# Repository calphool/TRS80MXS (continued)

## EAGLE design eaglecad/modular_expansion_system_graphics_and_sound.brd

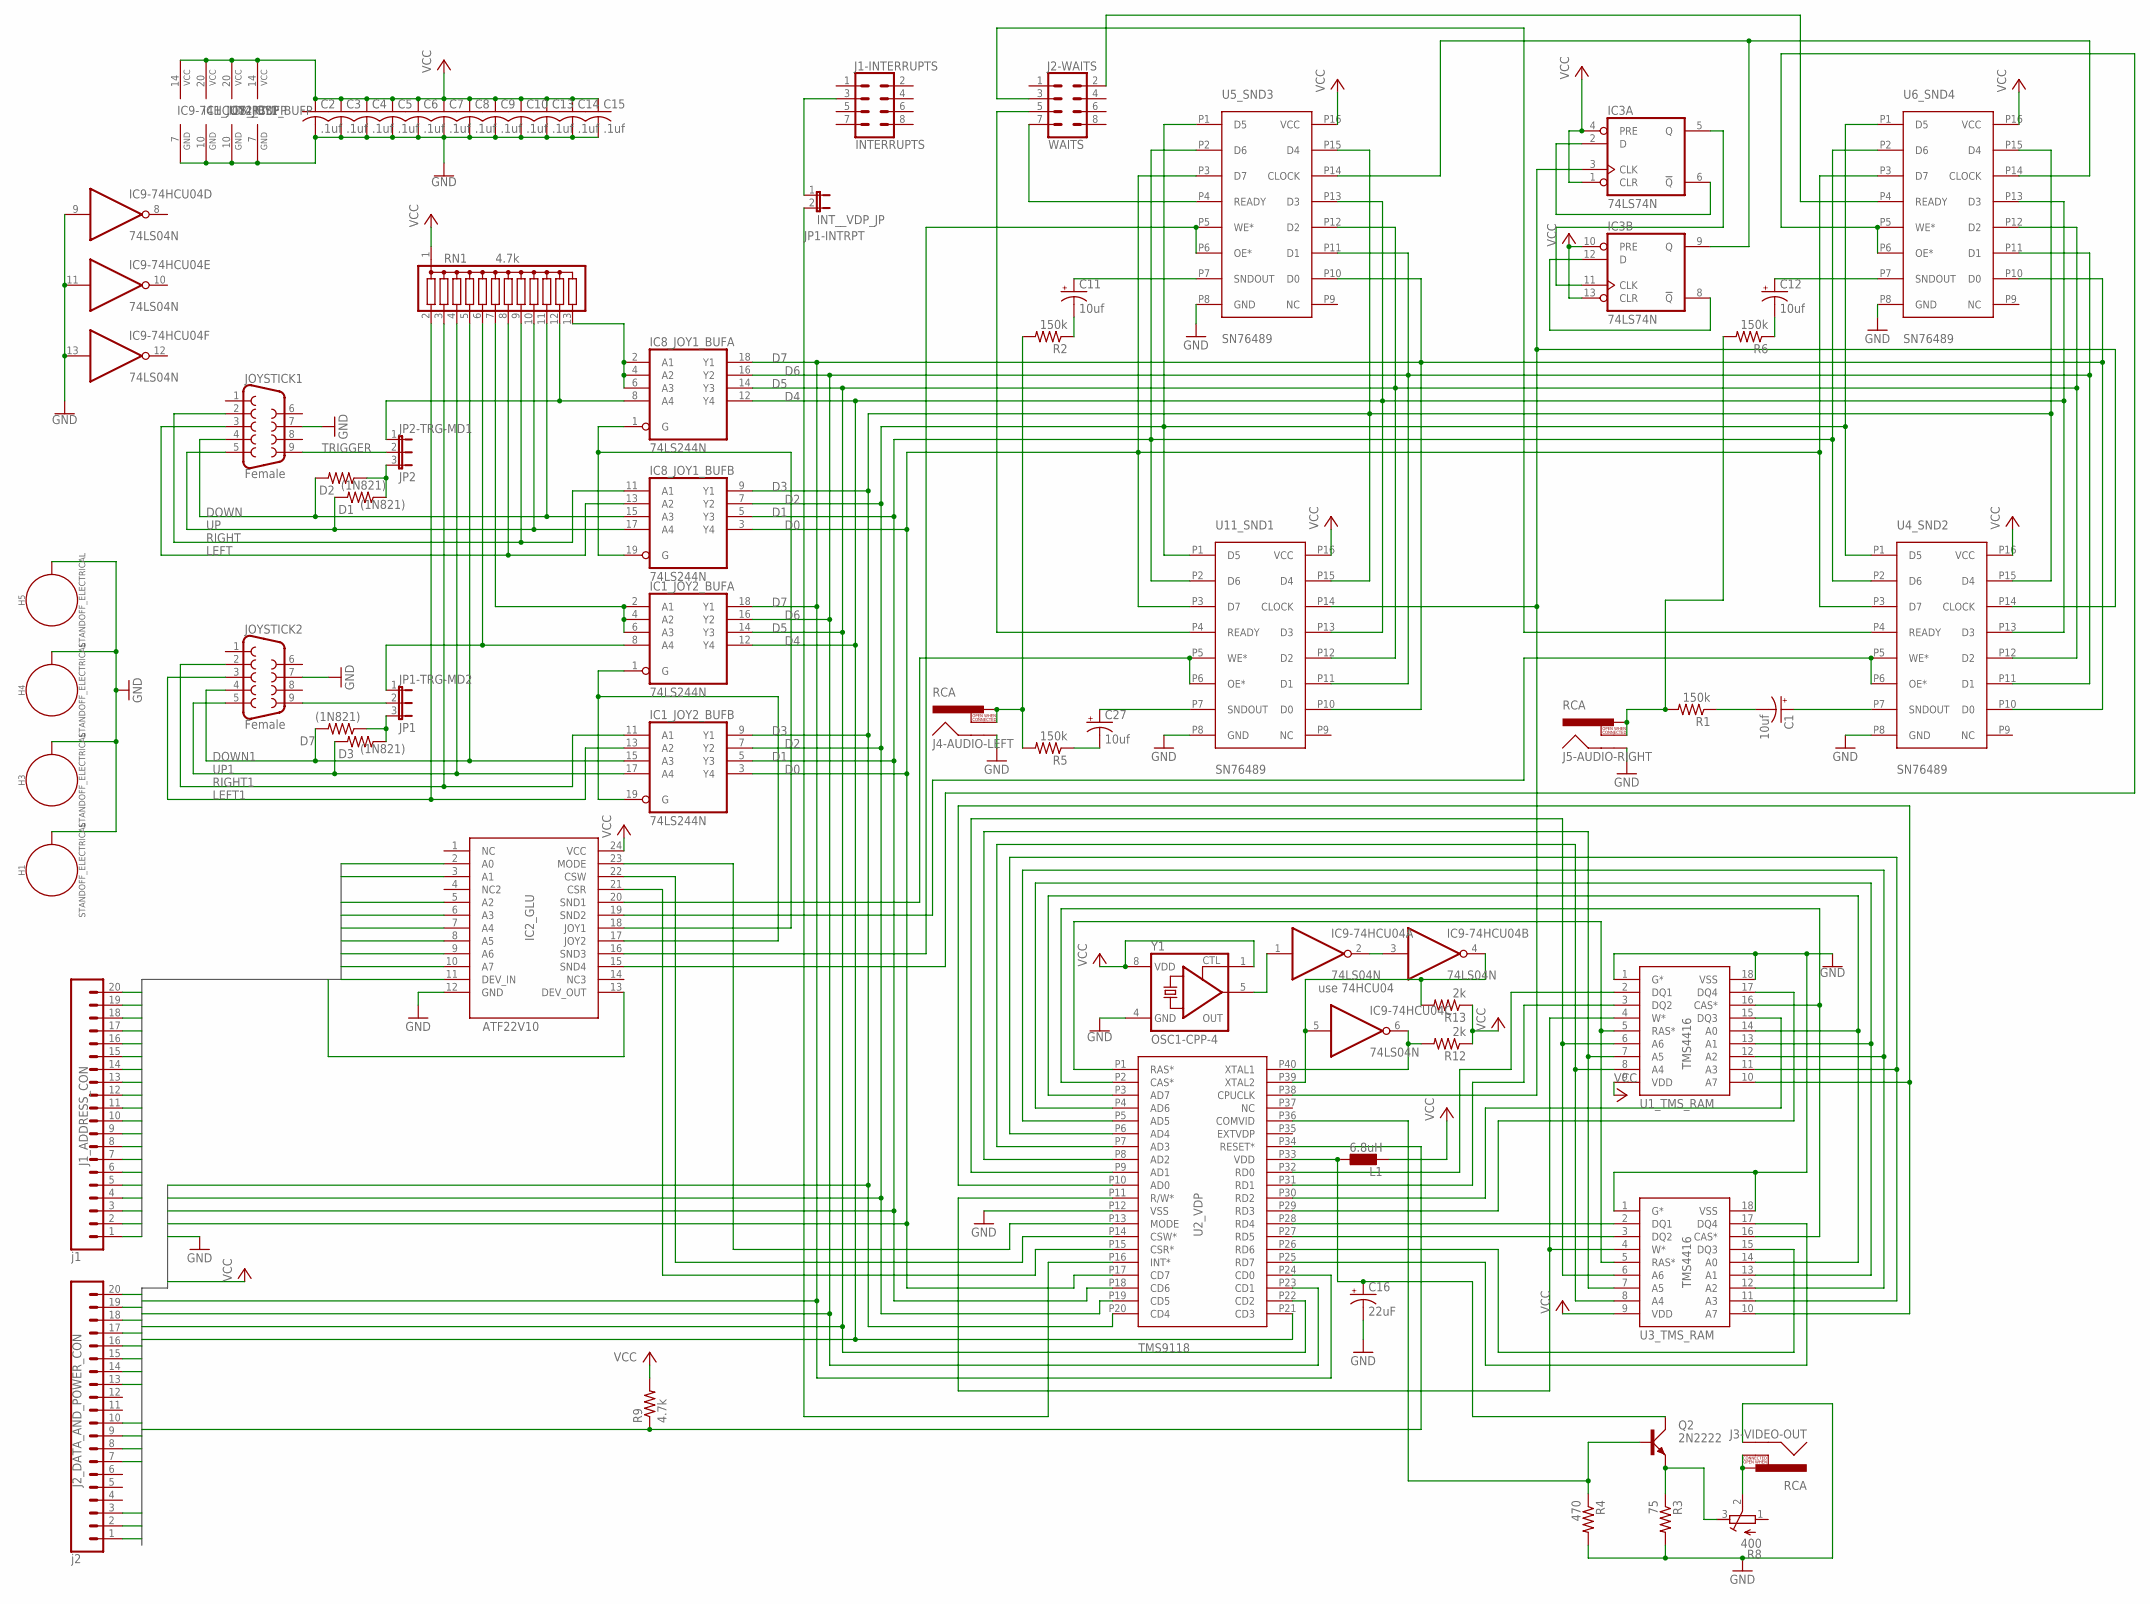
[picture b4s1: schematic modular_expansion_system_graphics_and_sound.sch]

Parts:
C1, C11, C12, C27: 10uf; E2,5-6
C2, C3, C4, C5, C6, C7, C8, C9, C10, C13, C14, C15: .1uf; C025-024X044
C16: 22uF; E2,5-5
D1, D2, D3, D7: (1N821); 0204V
H1, H3, H4, H5: STANDOFF_ELECTRICAL; STANDOFF-ELECTRICAL
IC1_JOY2_BUF, IC8_JOY1_BUF: 74LS244N; DIL20
IC2_GLU: ATF22V10; DIP24SKI
IC3: 74LS74N; DIL14
IC9-74HCU04: 74LS04N; DIL14
J1-INTERRUPTS: INTERRUPTS; 2X4
J1_ADDRESS_CON: j1; 1X20
J2-WAITS: WAITS; 2X4
J2_DATA_AND_POWER_CON: j2; 1X20
J3-VIDEO-OUT, J4-AUDIO-LEFT, J5-AUDIO-RIGHT: RCA
JOYSTICK1, JOYSTICK2: Female; DB9
JP1-INTRPT: INT__VDP_JP; JP1
JP1-TRG-MD2: JP1; JP2
JP2-TRG-MD1: JP2
L1: 6.8uH; 0207/10
Q2: 2N2222; TO18A
R1, R2, R5, R6: 150k; 0207/2V
R3: 75; 0207/2V
R4: 470; 0207/2V
R8: 400; RTRIM64W
R9: 4.7k; 0207/2V
R12, R13: 2k; 0207/2V
RN1: 4.7k; SIL13
U1_TMS_RAM, U3_TMS_RAM: TMS4416; DIP18
U2_VDP: TMS9118; DIP40_MCU
U4_SND2, U5_SND3, U6_SND4, U11_SND1: SN76489; DIP16
Y1: OSC1-CPP-4; CPP-4

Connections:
5_BIT_TRIGGER_LINE: IC8_JOY1_BUF.8 (A4), JP2-TRG-MD1.1, RN1.12
5_BIT_TRIGGER_LINE_2: IC1_JOY2_BUF.8 (A4), JP1-TRG-MD2.1, RN1.6
A0: IC2_GLU.2 (A0), J1_ADDRESS_CON.1
A1: IC2_GLU.3 (A1), J1_ADDRESS_CON.2
A2: IC2_GLU.5 (A2), J1_ADDRESS_CON.3
A3: IC2_GLU.6 (A3), J1_ADDRESS_CON.4
A4: IC2_GLU.7 (A4), J1_ADDRESS_CON.5
A5: IC2_GLU.8 (A5), J1_ADDRESS_CON.6
A6: IC2_GLU.9 (A6), J1_ADDRESS_CON.7
A7: IC2_GLU.10 (A7), J1_ADDRESS_CON.8
A8: J1_ADDRESS_CON.9
A9: J1_ADDRESS_CON.10
A10: J1_ADDRESS_CON.11
A11: J1_ADDRESS_CON.12
A12: J1_ADDRESS_CON.13
A13: J1_ADDRESS_CON.14
A14: J1_ADDRESS_CON.15
A15: J1_ADDRESS_CON.16
CAS*: J2_DATA_AND_POWER_CON.9
CLK-IN-1: IC9-74HCU04.6 (O), R12.2, U2_VDP.P40 (XTAL1)
CLK-IN-2: IC9-74HCU04.4 (O), IC9-74HCU04.5 (I), R13.2, U2_VDP.P39 (XTAL2)
CLK-OUT: IC9-74HCU04.1 (I), Y1.5 (OUT)
CLOCK_DIV_4: IC3.9 (Q), U5_SND3.P14 (CLOCK), U6_SND4.P14 (CLOCK)
COMVID: Q2.B, R4.1, U2_VDP.P36 (COMVID)
COMVID-OUT: Q2.E, R3.1, R8.3 (E)
CSR: IC2_GLU.21 (CSR), U2_VDP.P15 (CSR*)
CSW: IC2_GLU.22 (CSW), U2_VDP.P14 (CSW*)
D0: IC1_JOY2_BUF.3 (Y4), IC8_JOY1_BUF.3 (Y4), J2_DATA_AND_POWER_CON.20, U2_VDP.P17 (CD7), U4_SND2.P3 (D7), U5_SND3.P3 (D7), U6_SND4.P3 (D7), U11_SND1.P3 (D7)
D1: IC1_JOY2_BUF.5 (Y3), IC8_JOY1_BUF.5 (Y3), J2_DATA_AND_POWER_CON.19, U2_VDP.P18 (CD6), U4_SND2.P2 (D6), U5_SND3.P2 (D6), U6_SND4.P2 (D6), U11_SND1.P2 (D6)
D2: IC1_JOY2_BUF.7 (Y2), IC8_JOY1_BUF.7 (Y2), J2_DATA_AND_POWER_CON.18, U2_VDP.P19 (CD5), U4_SND2.P1 (D5), U5_SND3.P1 (D5), U6_SND4.P1 (D5), U11_SND1.P1 (D5)
D3: IC1_JOY2_BUF.9 (Y1), IC8_JOY1_BUF.9 (Y1), J2_DATA_AND_POWER_CON.17, U2_VDP.P20 (CD4), U4_SND2.P15 (D4), U5_SND3.P15 (D4), U6_SND4.P15 (D4), U11_SND1.P15 (D4)
D4: IC1_JOY2_BUF.12 (Y4), IC8_JOY1_BUF.12 (Y4), J2_DATA_AND_POWER_CON.16, U2_VDP.P21 (CD3), U4_SND2.P13 (D3), U5_SND3.P13 (D3), U6_SND4.P13 (D3), U11_SND1.P13 (D3)
D5: IC1_JOY2_BUF.14 (Y3), IC8_JOY1_BUF.14 (Y3), J2_DATA_AND_POWER_CON.15, U2_VDP.P22 (CD2), U4_SND2.P12 (D2), U5_SND3.P12 (D2), U6_SND4.P12 (D2), U11_SND1.P12 (D2)
D6: IC1_JOY2_BUF.16 (Y2), IC8_JOY1_BUF.16 (Y2), J2_DATA_AND_POWER_CON.14, U2_VDP.P23 (CD1), U4_SND2.P11 (D1), U5_SND3.P11 (D1), U6_SND4.P11 (D1), U11_SND1.P11 (D1)
D7: IC1_JOY2_BUF.18 (Y1), IC8_JOY1_BUF.18 (Y1), J2_DATA_AND_POWER_CON.13, U2_VDP.P24 (CD0), U4_SND2.P10 (D0), U5_SND3.P10 (D0), U6_SND4.P10 (D0), U11_SND1.P10 (D0)
DOWN: D2.2, IC8_JOY1_BUF.15 (A3), JOYSTICK1.4, RN1.11
DOWN1: D7.2, IC1_JOY2_BUF.15 (A3), JOYSTICK2.4, RN1.5
GND: C2.2, C3.2, C4.2, C5.2, C6.2, C7.2, C8.2, C9.2, C10.2, C13.2, C14.2, C15.2, C16.-, H1.P1, H3.P1, H4.P1, H5.P1, IC1_JOY2_BUF.10 (GND), IC2_GLU.12 (GND), IC3.7 (GND), IC8_JOY1_BUF.10 (GND), IC9-74HCU04.7 (GND), IC9-74HCU04.9 (I), IC9-74HCU04.11 (I), IC9-74HCU04.13 (I), J2_DATA_AND_POWER_CON.2, J3-VIDEO-OUT.SHELL, J4-AUDIO-LEFT.SHELL, J5-AUDIO-RIGHT.SHELL, JOYSTICK1.7, JOYSTICK2.7, R3.2, R4.2, U1_TMS_RAM.1 (G*), U1_TMS_RAM.18 (VSS), U2_VDP.P12 (VSS), U3_TMS_RAM.1 (G*), U3_TMS_RAM.18 (VSS), U4_SND2.P8 (GND), U5_SND3.P8 (GND), U6_SND4.P8 (GND), U11_SND1.P8 (GND), Y1.4 (GND)
IN*: IC2_GLU.11 (DEV_IN), J1_ADDRESS_CON.17
INTAK*: J2_DATA_AND_POWER_CON.7
JOY1_IN_ENABLE_N: IC2_GLU.18 (JOY1), IC8_JOY1_BUF.1 (G), IC8_JOY1_BUF.19 (G)
JOY2_IN_ENABLE_N: IC1_JOY2_BUF.1 (G), IC1_JOY2_BUF.19 (G), IC2_GLU.17 (JOY2)
LEFT: IC8_JOY1_BUF.13 (A2), JOYSTICK1.3, RN1.8
LEFT1: IC1_JOY2_BUF.13 (A2), JOYSTICK2.3, RN1.2
unnamed: J4-AUDIO-LEFT.PIN, J4-AUDIO-LEFT.SWITCH, R2.2, R5.2
unnamed: J1-INTERRUPTS.3, JP1-INTRPT.1
unnamed: JP1-INTRPT.2, U2_VDP.P16 (INT*)
unnamed: J3-VIDEO-OUT.PIN, J3-VIDEO-OUT.SWITCH, R8.2 (S)
unnamed: C12.-, R6.1
unnamed: IC3.5 (Q), IC3.11 (CLK)
unnamed: IC3.8 (!Q), IC3.12 (D)
unnamed: C11.+, U5_SND3.P7 (SNDOUT)
unnamed: IC9-74HCU04.2 (O), IC9-74HCU04.3 (I)
unnamed: C12.+, U6_SND4.P7 (SNDOUT)
unnamed: IC3.2 (D), IC3.6 (!Q)
unnamed: C1.-, R1.1
unnamed: C11.-, R2.1
unnamed: U1_TMS_RAM.5 (RAS*), U2_VDP.P1 (RAS*), U3_TMS_RAM.5 (RAS*)
unnamed: U1_TMS_RAM.16 (CAS*), U2_VDP.P2 (CAS*), U3_TMS_RAM.16 (CAS*)
unnamed: J5-AUDIO-RIGHT.PIN, J5-AUDIO-RIGHT.SWITCH, R1.2, R6.2
unnamed: C27.-, R5.1
OUT*: IC2_GLU.13 (DEV_OUT), J1_ADDRESS_CON.18
RAS*: J2_DATA_AND_POWER_CON.10
RD*: J1_ADDRESS_CON.19
RIGHT: IC8_JOY1_BUF.11 (A1), JOYSTICK1.2, RN1.9
RIGHT1: IC1_JOY2_BUF.11 (A1), JOYSTICK2.2, RN1.3
SN76489-CLOCK: IC3.3 (CLK), U2_VDP.P38 (CPUCLK), U4_SND2.P14 (CLOCK), U11_SND1.P14 (CLOCK)
SND1_ENABLE_N: IC2_GLU.20 (SND1), U11_SND1.P5 (WE*), U11_SND1.P6 (OE*)
SND1_READY: J2-WAITS.5, U11_SND1.P4 (READY)
SND2_ENABLE_N: IC2_GLU.19 (SND2), U4_SND2.P5 (WE*), U4_SND2.P6 (OE*)
SND2_READY: J2-WAITS.3, U4_SND2.P4 (READY)
SND3_ENABLE_N: IC2_GLU.16 (SND3), U5_SND3.P5 (WE*), U5_SND3.P6 (OE*)
SND3_READY: J2-WAITS.7, U5_SND3.P4 (READY)
SND4_ENABLE_N: IC2_GLU.15 (SND4), U6_SND4.P5 (WE*), U6_SND4.P6 (OE*)
SND4_READY: J2-WAITS.2, U6_SND4.P4 (READY)
SNDOUT1: C27.+, U11_SND1.P7 (SNDOUT)
SNDOUT2: C1.+, U4_SND2.P7 (SNDOUT)
SYSRES*: J2_DATA_AND_POWER_CON.8, R9.1, U2_VDP.P34 (RESET*)
TIED-HIGH-1: IC8_JOY1_BUF.2 (A1), IC8_JOY1_BUF.4 (A2), IC8_JOY1_BUF.6 (A3), RN1.13
TIED-HIGH-2: IC1_JOY2_BUF.2 (A1), IC1_JOY2_BUF.4 (A2), IC1_JOY2_BUF.6 (A3), RN1.7
TMS9118_RW(*)_TMS4416_W(*): U1_TMS_RAM.4 (W*), U2_VDP.P11 (R/W*), U3_TMS_RAM.4 (W*)
TMS9918_AD0-TMS4416_A7: U1_TMS_RAM.10 (A7), U2_VDP.P10 (AD0), U3_TMS_RAM.10 (A7)
TMS9918_AD1-TMS4416_A6: U1_TMS_RAM.6 (A6), U2_VDP.P9 (AD1), U3_TMS_RAM.6 (A6)
TMS9918_AD2-TMS4416_A5: U1_TMS_RAM.7 (A5), U2_VDP.P8 (AD2), U3_TMS_RAM.7 (A5)
TMS9918_AD3-TMS4416_A4: U1_TMS_RAM.8 (A4), U2_VDP.P7 (AD3), U3_TMS_RAM.8 (A4)
TMS9918_AD4-TMS4416_A3: U1_TMS_RAM.11 (A3), U2_VDP.P6 (AD4), U3_TMS_RAM.11 (A3)
TMS9918_AD5-TMS4416_A2: U1_TMS_RAM.12 (A2), U2_VDP.P5 (AD5), U3_TMS_RAM.12 (A2)
TMS9918_AD6-TMS4416_A1: U1_TMS_RAM.13 (A1), U2_VDP.P4 (AD6), U3_TMS_RAM.13 (A1)
TMS9918_AD7-TMS4416_A0: U1_TMS_RAM.14 (A0), U2_VDP.P3 (AD7), U3_TMS_RAM.14 (A0)
TOPOFDIODES: D1.1, D2.1, JP2-TRG-MD1.3
TOPOFDIODES1: D3.1, D7.1, JP1-TRG-MD2.3
TRIGGER: JOYSTICK1.9, JP2-TRG-MD1.2
TRIGGER1: JOYSTICK2.9, JP1-TRG-MD2.2
UP: D1.2, IC8_JOY1_BUF.17 (A4), JOYSTICK1.5, RN1.10
UP1: D3.2, IC1_JOY2_BUF.17 (A4), JOYSTICK2.5, RN1.4
VCC: C2.1, C3.1, C4.1, C5.1, C6.1, C7.1, C8.1, C9.1, C10.1, C13.1, C14.1, C15.1, IC1_JOY2_BUF.20 (VCC), IC2_GLU.24 (VCC), IC3.1 (CLR), IC3.4 (PRE), IC3.10 (PRE), IC3.13 (CLR), IC3.14 (VCC), IC8_JOY1_BUF.20 (VCC), IC9-74HCU04.14 (VCC), J2_DATA_AND_POWER_CON.1, L1.2, R9.2, R12.1, R13.1, RN1.1, U1_TMS_RAM.9 (VDD), U3_TMS_RAM.9 (VDD), U4_SND2.P16 (VCC), U5_SND3.P16 (VCC), U6_SND4.P16 (VCC), U11_SND1.P16 (VCC), Y1.1 (CTL), Y1.8 (VDD)
VCC/2: J2_DATA_AND_POWER_CON.3
VDP-RD0: U1_TMS_RAM.2 (DQ1), U2_VDP.P32 (RD0)
VDP-RD1: U1_TMS_RAM.3 (DQ2), U2_VDP.P31 (RD1)
VDP-RD2: U1_TMS_RAM.15 (DQ3), U2_VDP.P30 (RD2)
VDP-RD3: U1_TMS_RAM.17 (DQ4), U2_VDP.P29 (RD3)
VDP-RD4: U2_VDP.P28 (RD4), U3_TMS_RAM.2 (DQ1)
VDP-RD5: U2_VDP.P27 (RD5), U3_TMS_RAM.3 (DQ2)
VDP-RD6: U2_VDP.P26 (RD6), U3_TMS_RAM.15 (DQ3)
VDP-RD7: U2_VDP.P25 (RD7), U3_TMS_RAM.17 (DQ4)
VDP_MODE: IC2_GLU.23 (MODE), U2_VDP.P13 (MODE)
VID-VCC: C16.+, L1.1, Q2.C, U2_VDP.P33 (VDD)
WR*: J1_ADDRESS_CON.20

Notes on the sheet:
use 74HCU04

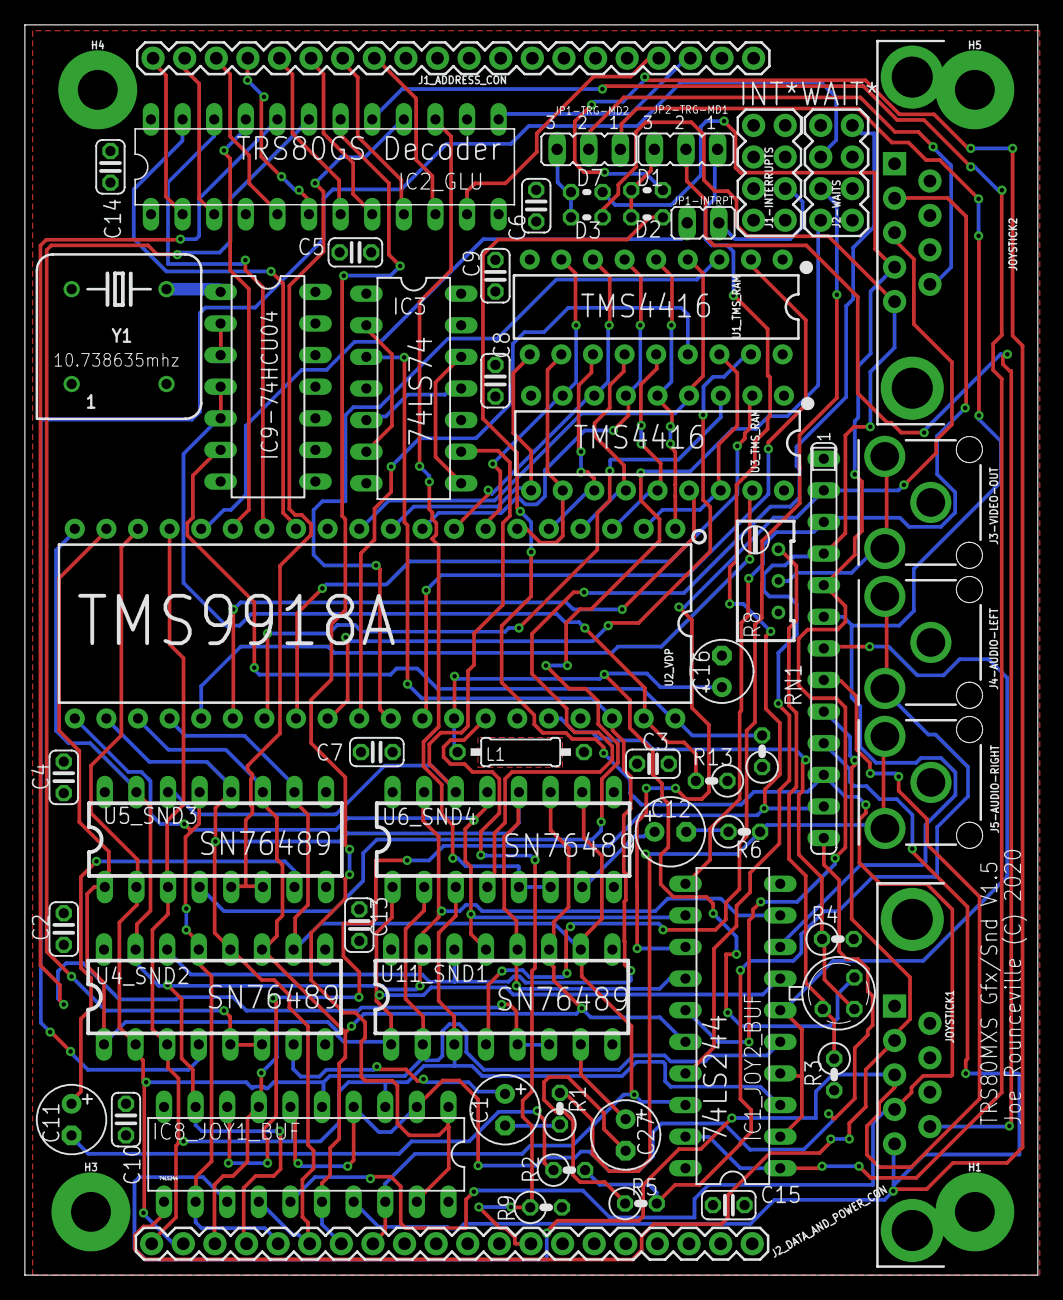
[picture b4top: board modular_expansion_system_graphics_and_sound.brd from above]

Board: 2 copper layers, 81.4 x 100.5 mm, 63 parts (0 on the bottom side), 94 nets.

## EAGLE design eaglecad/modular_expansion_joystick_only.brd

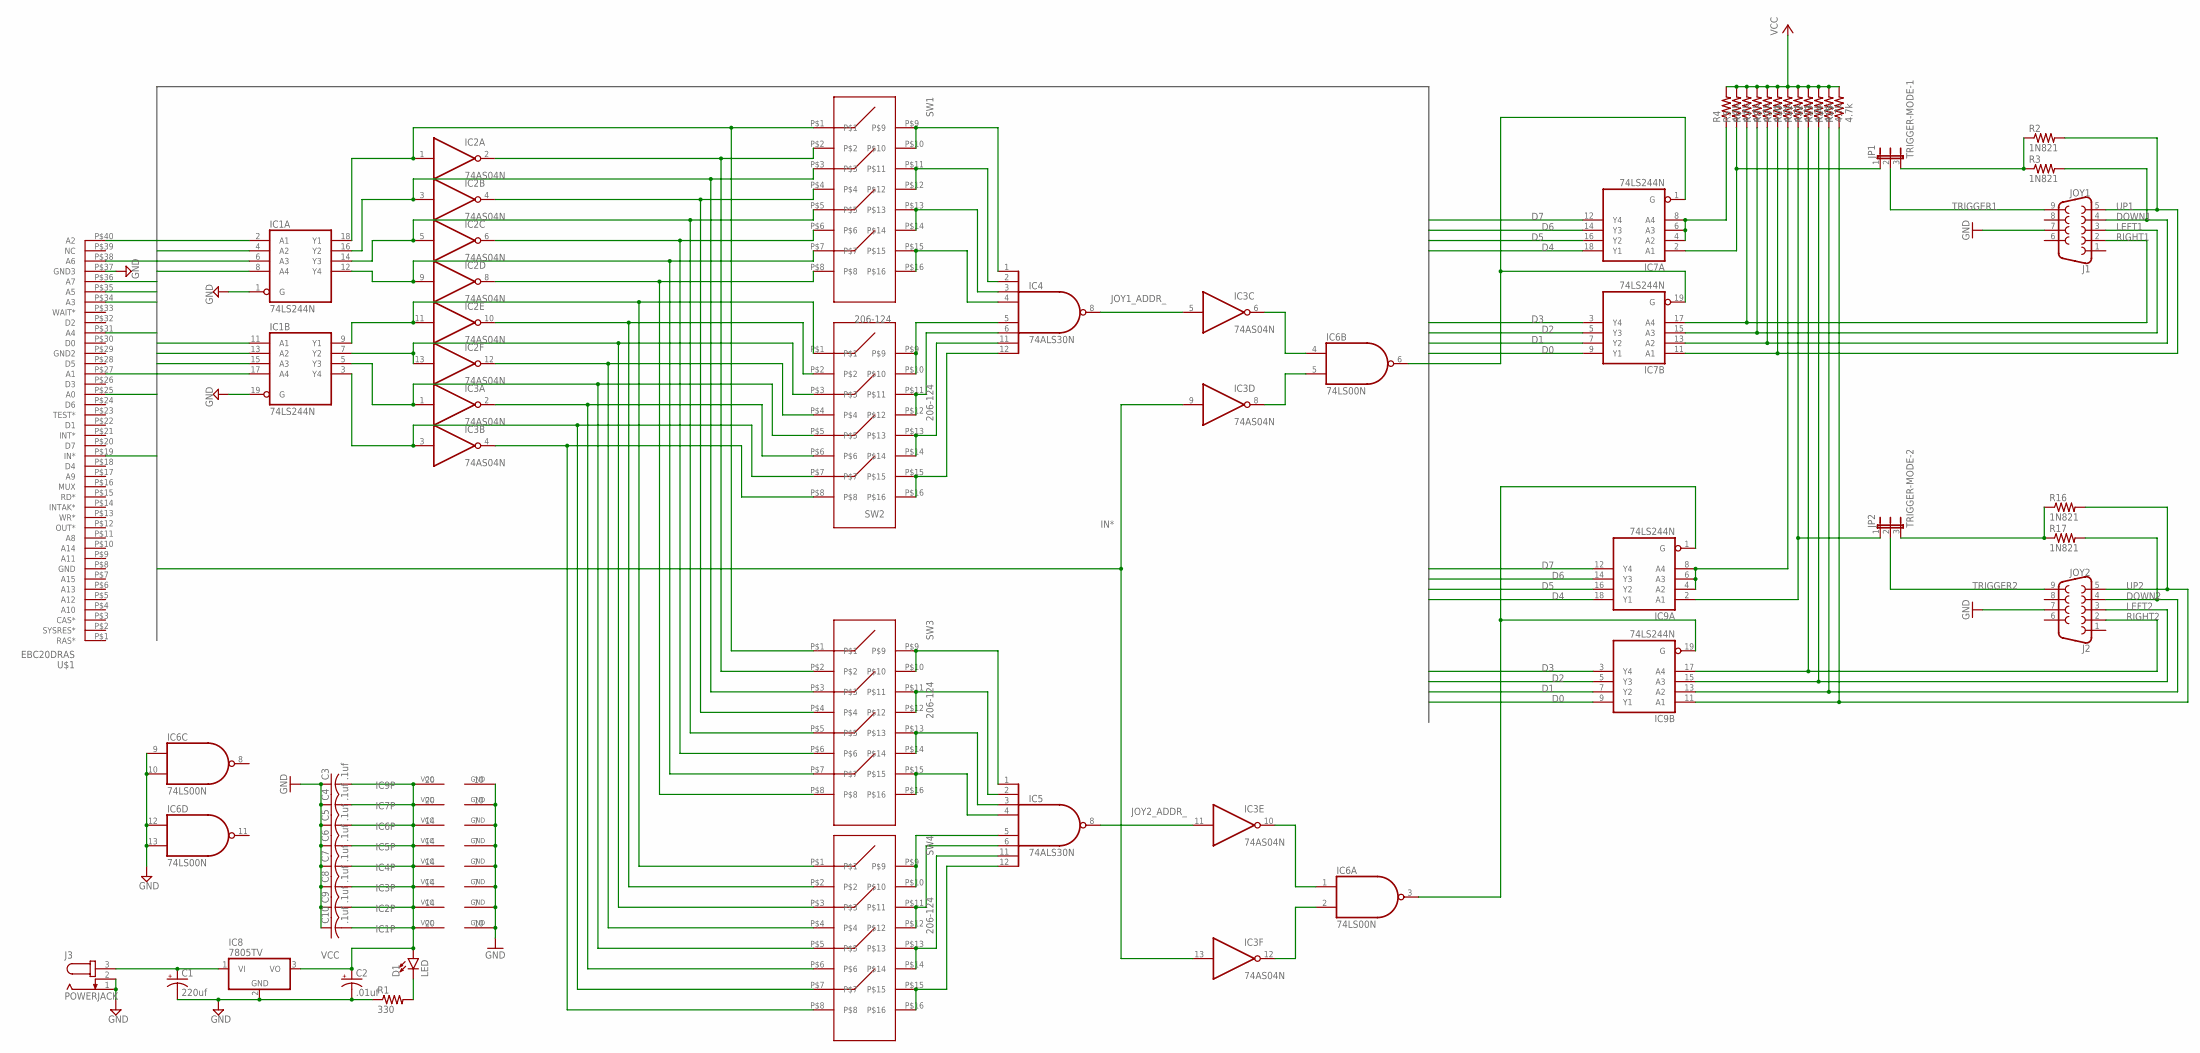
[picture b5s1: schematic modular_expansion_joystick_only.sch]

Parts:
C1: 220uf; E3,5-10
C2: .01uf; E2,5-6E
C3, C4, C5, C6, C7, C8, C9, C10: .1uf; C025-025X050
D1: LED; LED_3MM
IC1, IC7, IC9: 74LS244N; DIL20
IC2, IC3: 74AS04N; DIL14
IC4, IC5: 74ALS30N; DIL14
IC6: 74LS00N; DIL14
IC8: 7805TV; TO220V
J1: JOY1; DB9
J2: JOY2; DB9
J3: POWERJACK; SPC4077
JP1: TRIGGER-MODE-1; JP2
JP2: TRIGGER-MODE-2; JP2
R1: 330; 0204V
R2, R3, R16, R17: 1N821; 0204V
R4, R5, R6, R7, R8, R9, R10, R11, R12, R13, R14, R15: 4.7k; 0204/5
SW1, SW2, SW3, SW4: 206-124
U$1: EBC20DRAS

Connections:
A0: IC1.2 (A1), U$1.P$25 (A0)
A1: IC1.4 (A2), U$1.P$27 (A1)
A2: IC1.6 (A3), U$1.P$40 (A2)
A3: IC1.8 (A4), U$1.P$34 (A3)
A4: IC1.11 (A1), U$1.P$31 (A4)
A5: IC1.13 (A2), U$1.P$35 (A5)
A6: IC1.15 (A3), U$1.P$38 (A6)
A7: IC1.17 (A4), U$1.P$36 (A7)
D0: IC7.9 (Y1), IC9.9 (Y1)
D1: IC7.7 (Y2), IC9.7 (Y2)
D2: IC7.5 (Y3), IC9.5 (Y3)
D3: IC7.3 (Y4), IC9.3 (Y4)
D4: IC7.18 (Y1), IC9.18 (Y1)
D5: IC7.16 (Y2), IC9.16 (Y2)
D6: IC7.14 (Y3), IC9.14 (Y3)
D7: IC7.12 (Y4), IC9.12 (Y4)
DOWN1: IC7.13 (A2), J1.4, R3.2, R8.1
DOWN2: IC9.13 (A2), J2.4, R14.1, R17.2
GND: C1.-, C2.-, C3.1, C4.1, C5.1, C6.1, C7.1, C8.1, C9.1, C10.1, IC1.1 (G), IC1.10 (GND), IC1.19 (G), IC2.7 (GND), IC3.7 (GND), IC4.7 (GND), IC5.7 (GND), IC6.7 (GND), IC6.9 (I0), IC6.10 (I1), IC6.12 (I0), IC6.13 (I1), IC7.10 (GND), IC8.2 (GND), IC9.10 (GND), J1.7, J2.7, J3.1, J3.2, R1.1, U$1.P$37 (GND3)
IN*: IC3.9 (I), IC3.13 (I), U$1.P$19 (IN*)
JOY1_ADDR_: IC3.5 (I), IC4.8 (O)
JOY1_SELECTED_: IC6.6 (O), IC7.1 (G), IC7.19 (G)
JOY2_ADDR_: IC3.11 (I), IC5.8 (O)
JOY2_SELECTED_: IC6.3 (O), IC9.1 (G), IC9.19 (G)
LEFT1: IC7.15 (A3), J1.3, R7.1
LEFT2: IC9.15 (A3), J2.3, R13.1
unnamed: IC1.18 (Y1), IC2.1 (I), SW1.P$1, SW3.P$1
unnamed: IC1.16 (Y2), IC2.3 (I), SW1.P$3, SW3.P$3
unnamed: IC1.14 (Y3), IC2.5 (I), SW1.P$5, SW3.P$5
unnamed: IC1.12 (Y4), IC2.9 (I), SW1.P$7, SW3.P$7
unnamed: IC1.9 (Y1), IC2.11 (I), SW2.P$1, SW4.P$1
unnamed: IC1.7 (Y2), IC2.13 (I), SW2.P$3, SW4.P$3
unnamed: IC1.5 (Y3), IC3.1 (I), SW2.P$5, SW4.P$5
unnamed: IC1.3 (Y4), IC3.3 (I), SW2.P$7, SW4.P$7
unnamed: IC2.2 (O), SW1.P$2, SW3.P$2
unnamed: IC2.4 (O), SW1.P$4, SW3.P$4
unnamed: IC2.6 (O), SW1.P$6, SW3.P$6
unnamed: IC2.8 (O), SW1.P$8, SW3.P$8
unnamed: IC2.10 (O), SW2.P$2, SW4.P$2
unnamed: IC2.12 (O), SW2.P$4, SW4.P$4
unnamed: IC3.2 (O), SW2.P$6, SW4.P$6
unnamed: IC4.1 (I0), SW1.P$9, SW1.P$10
unnamed: IC4.2 (I1), SW1.P$11, SW1.P$12
unnamed: IC4.3 (I2), SW1.P$13, SW1.P$14
unnamed: IC3.4 (O), SW2.P$8, SW4.P$8
unnamed: IC4.4 (I3), SW1.P$15, SW1.P$16
unnamed: IC4.5 (I4), SW2.P$9, SW2.P$10
unnamed: IC4.6 (I5), SW2.P$11, SW2.P$12
unnamed: IC4.11 (I6), SW2.P$13, SW2.P$14
unnamed: IC4.12 (I7), SW2.P$15, SW2.P$16
unnamed: IC3.6 (O), IC6.4 (I0)
unnamed: IC3.8 (O), IC6.5 (I1)
unnamed: IC3.12 (O), IC6.2 (I1)
unnamed: IC3.10 (O), IC6.1 (I0)
unnamed: IC5.1 (I0), SW3.P$9, SW3.P$10
unnamed: IC5.2 (I1), SW3.P$11, SW3.P$12
unnamed: IC5.3 (I2), SW3.P$13, SW3.P$14
unnamed: IC5.4 (I3), SW3.P$15, SW3.P$16
unnamed: IC5.5 (I4), SW4.P$9, SW4.P$10
unnamed: IC5.6 (I5), SW4.P$11, SW4.P$12
unnamed: IC5.11 (I6), SW4.P$13, SW4.P$14
unnamed: IC5.12 (I7), SW4.P$15, SW4.P$16
unnamed: JP2.3, R16.1, R17.1
unnamed: C1.+, IC8.1 (VI), J3.3
unnamed: JP1.3, R2.1, R3.1
unnamed: IC9.4 (A2), IC9.6 (A3), IC9.8 (A4), R10.1
unnamed: D1.K (C), R1.2
unnamed: IC9.2 (A1), JP2.1, R11.1
unnamed: IC7.4 (A2), IC7.6 (A3), IC7.8 (A4), R4.1
unnamed: IC7.2 (A1), JP1.1, R5.1
RIGHT1: IC7.17 (A4), J1.2, R6.1
RIGHT2: IC9.17 (A4), J2.2, R12.1
TRIGGER1: J1.9, JP1.2
TRIGGER2: J2.9, JP2.2
UP1: IC7.11 (A1), J1.5, R2.2, R9.1
UP2: IC9.11 (A1), J2.5, R15.1, R16.2
VCC: C2.+, C3.2, C4.2, C5.2, C6.2, C7.2, C8.2, C9.2, C10.2, D1.A, IC1.20 (VCC), IC2.14 (VCC), IC3.14 (VCC), IC4.14 (VCC), IC5.14 (VCC), IC6.14 (VCC), IC7.20 (VCC), IC8.3 (VO), IC9.20 (VCC), R4.2, R5.2, R6.2, R7.2, R8.2, R9.2, R10.2, R11.2, R12.2, R13.2, R14.2, R15.2

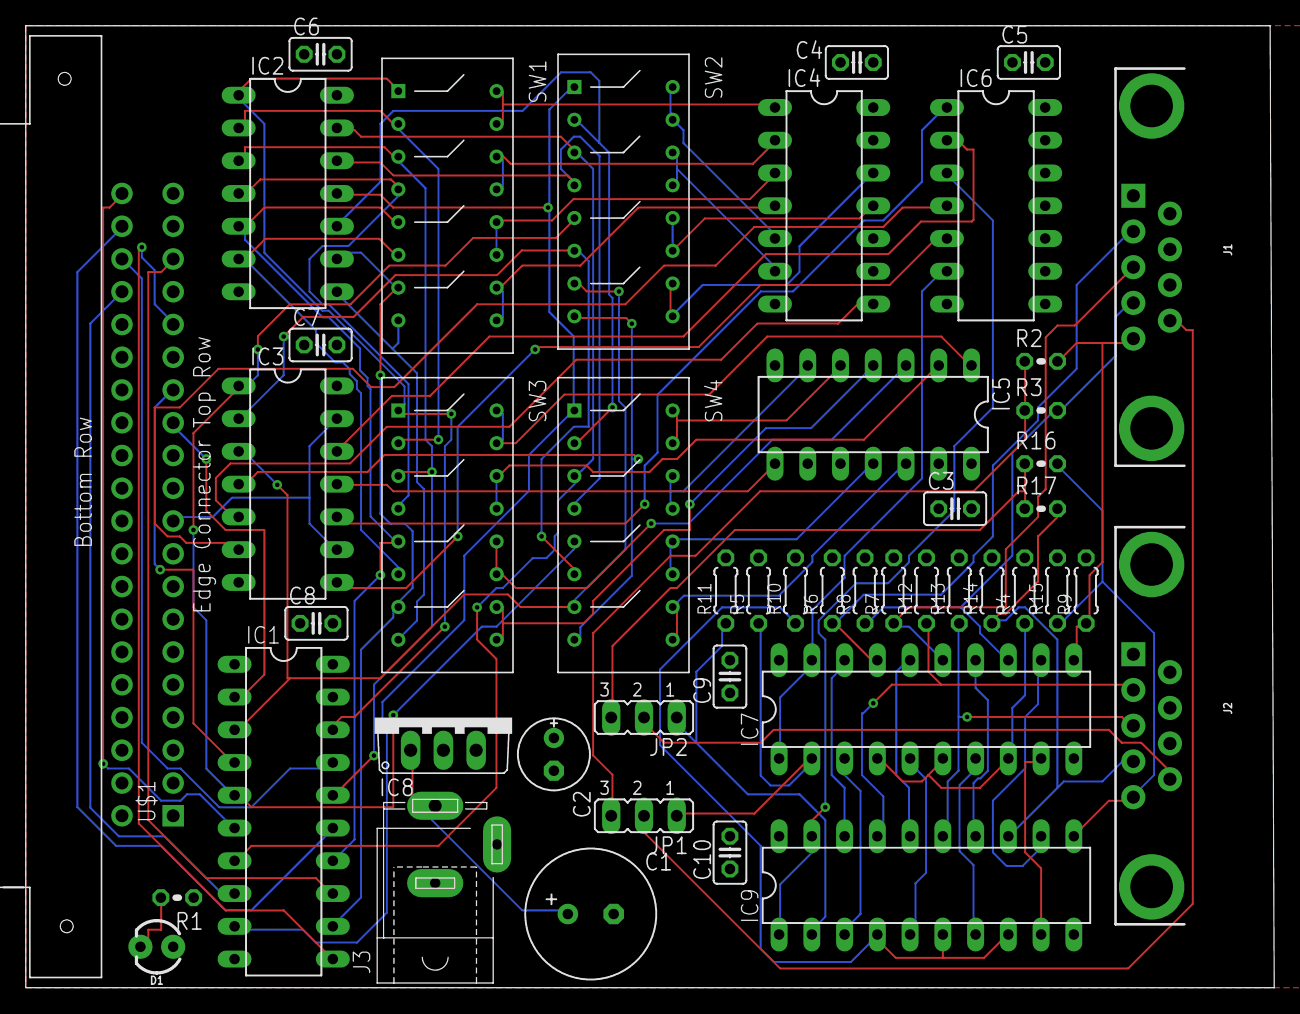
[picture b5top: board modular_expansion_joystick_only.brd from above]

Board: 2 copper layers, 96.8 x 74.6 mm, 47 parts (0 on the bottom side), 77 nets.

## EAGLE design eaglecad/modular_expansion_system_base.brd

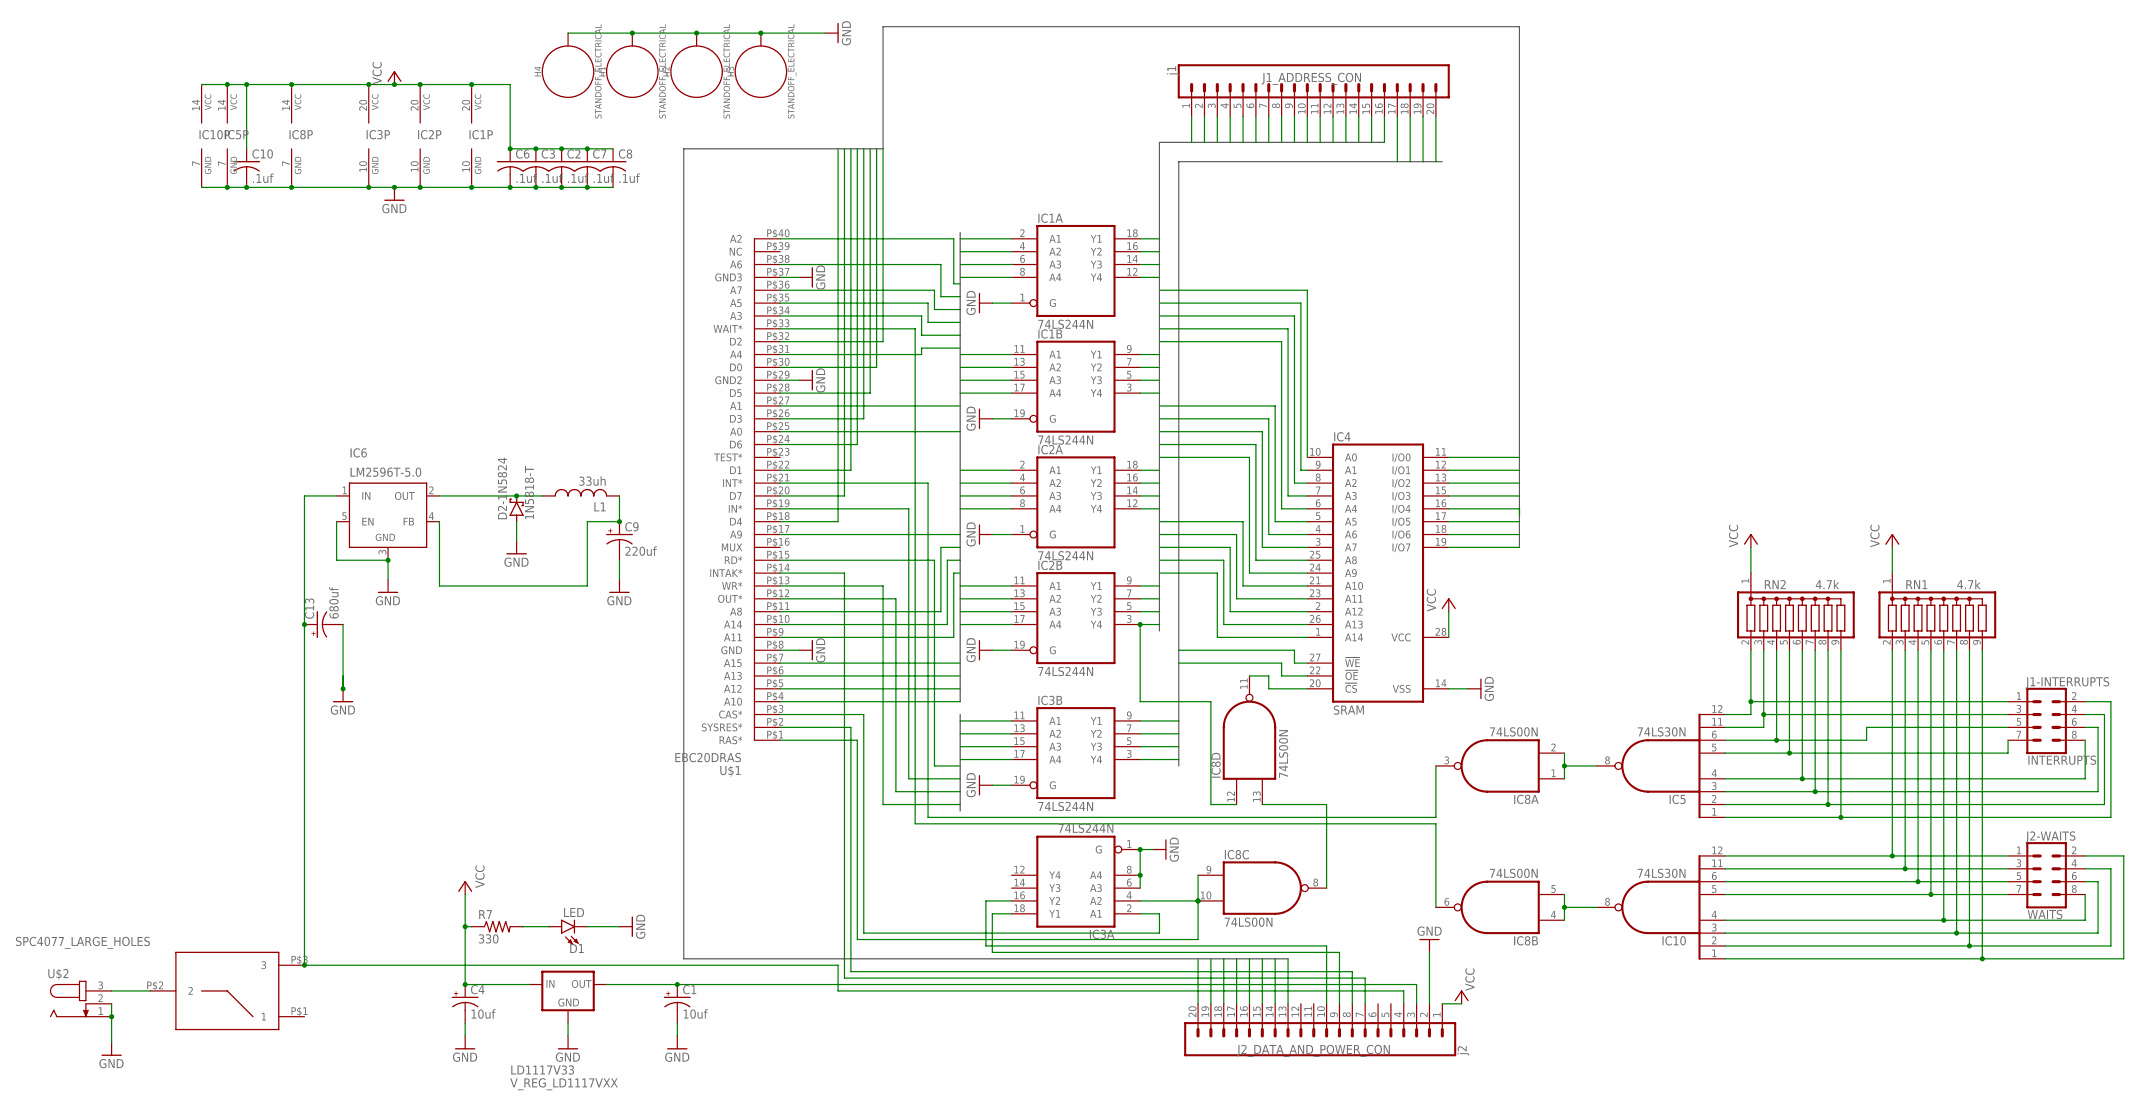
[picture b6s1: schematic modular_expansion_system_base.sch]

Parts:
C1, C4: 10uf; E2,5-5
C2, C3, C6, C7, C8, C10: .1uf; C025-025X050
C9: 220uf; E2,5-5
C13: 680uf; E3,5-8
D1: LED; LED_3MM
D2-1N5824: 1N5818-T; DO41-7.6
H1, H2, H3, H4: STANDOFF_ELECTRICAL; STANDOFF-ELECTRICAL
IC1, IC2, IC3: 74LS244N; DIL20
IC4: SRAM; DIL28-6
IC5, IC10: 74LS30N; DIL14
IC6: LM2596T-5.0; TO220-52
IC8: 74LS00N; DIL14
J1-INTERRUPTS: INTERRUPTS; 2X4
J1_ADDRESS_CON: j1; 1X20
J2-WAITS: WAITS; 2X4
J2_DATA_AND_POWER_CON: j2; 1X20
L1: 33uh; 6000-XXXX-RC
LD1117V33: V_REG_LD1117VXX; 78XXL
R7: 330; 0309V
RN1, RN2: 4.7k; SIL9
SW1: 100SP3T1B1M6QE
U$1: EBC20DRAS
U$2: SPC4077_LARGE_HOLES; SPC4077

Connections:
5V_FROM_SWITCHER: C9.+, IC6.4 (FB), L1.2
9V-IN: SW1.P$2 (2), U$2.3
9V-POST-SW: C13.+, IC6.1 (IN), J2_DATA_AND_POWER_CON.4, SW1.P$3 (3)
A0: IC1.2 (A1), U$1.P$25 (A0)
A1: IC1.4 (A2), U$1.P$27 (A1)
A2: IC1.6 (A3), U$1.P$40 (A2)
A3: IC1.8 (A4), U$1.P$34 (A3)
A4: IC1.11 (A1), U$1.P$31 (A4)
A5: IC1.13 (A2), U$1.P$35 (A5)
A6: IC1.15 (A3), U$1.P$38 (A6)
A7: IC1.17 (A4), U$1.P$36 (A7)
A8: IC2.2 (A1), U$1.P$11 (A8)
A9: IC2.4 (A2), U$1.P$17 (A9)
A10: IC2.6 (A3), U$1.P$4 (A10)
A11: IC2.8 (A4), U$1.P$9 (A11)
A12: IC2.11 (A1), U$1.P$5 (A12)
A13: IC2.13 (A2), U$1.P$6 (A13)
A14: IC2.15 (A3), U$1.P$10 (A14)
A15: IC2.17 (A4), U$1.P$7 (A15)
A15_AND_RAS: IC4.20 (!CS), IC8.11 (O)
BUFFERED_A0: IC1.18 (Y1), IC4.10 (A0), J1_ADDRESS_CON.1
BUFFERED_A1: IC1.16 (Y2), IC4.9 (A1), J1_ADDRESS_CON.2
BUFFERED_A2: IC1.14 (Y3), IC4.8 (A2), J1_ADDRESS_CON.3
BUFFERED_A3: IC1.12 (Y4), IC4.7 (A3), J1_ADDRESS_CON.4
BUFFERED_A4: IC1.9 (Y1), IC4.6 (A4), J1_ADDRESS_CON.5
BUFFERED_A5: IC1.7 (Y2), IC4.5 (A5), J1_ADDRESS_CON.6
BUFFERED_A6: IC1.5 (Y3), IC4.4 (A6), J1_ADDRESS_CON.7
BUFFERED_A7: IC1.3 (Y4), IC4.3 (A7), J1_ADDRESS_CON.8
BUFFERED_A8: IC2.18 (Y1), IC4.25 (A8), J1_ADDRESS_CON.9
BUFFERED_A9: IC2.16 (Y2), IC4.24 (A9), J1_ADDRESS_CON.10
BUFFERED_A10: IC2.14 (Y3), IC4.21 (A10), J1_ADDRESS_CON.11
BUFFERED_A11: IC2.12 (Y4), IC4.23 (A11), J1_ADDRESS_CON.12
BUFFERED_A12: IC2.9 (Y1), IC4.2 (A12), J1_ADDRESS_CON.13
BUFFERED_A13: IC2.7 (Y2), IC4.26 (A13), J1_ADDRESS_CON.14
BUFFERED_A14: IC2.5 (Y3), IC4.1 (A14), J1_ADDRESS_CON.15
BUFFERED_A15: IC2.3 (Y4), IC8.12 (I0), J1_ADDRESS_CON.16
BUFFERED_CAS*: IC3.18 (Y1), J2_DATA_AND_POWER_CON.9
BUFFERED_IN*: IC3.5 (Y3), J1_ADDRESS_CON.17
BUFFERED_OUT*: IC3.3 (Y4), J1_ADDRESS_CON.18
BUFFERED_RAS*: IC3.16 (Y2), J2_DATA_AND_POWER_CON.10
BUFFERED_RD*: IC3.9 (Y1), IC4.22 (!OE), J1_ADDRESS_CON.19
BUFFERED_WR*: IC3.7 (Y2), IC4.27 (!WE), J1_ADDRESS_CON.20
CAS*: IC3.2 (A1), U$1.P$3 (CAS*)
D0: IC4.11 (I/O0), J2_DATA_AND_POWER_CON.20, U$1.P$30 (D0)
D1: IC4.12 (I/O1), J2_DATA_AND_POWER_CON.19, U$1.P$22 (D1)
D2: IC4.13 (I/O2), J2_DATA_AND_POWER_CON.18, U$1.P$32 (D2)
D3: IC4.15 (I/O3), J2_DATA_AND_POWER_CON.17, U$1.P$26 (D3)
D4: IC4.16 (I/O4), J2_DATA_AND_POWER_CON.16, U$1.P$18 (D4)
D5: IC4.17 (I/O5), J2_DATA_AND_POWER_CON.15, U$1.P$28 (D5)
D6: IC4.18 (I/O6), J2_DATA_AND_POWER_CON.14, U$1.P$24 (D6)
D7: IC4.19 (I/O7), J2_DATA_AND_POWER_CON.13, U$1.P$20 (D7)
GND: C1.-, C2.2, C3.2, C4.-, C6.2, C7.2, C8.2, C9.-, C10.2, C13.-, D1.K (C), D2-1N5824.A, H1.P1, H2.P1, H3.P1, H4.P1, IC1.1 (G), IC1.10 (GND), IC1.19 (G), IC2.1 (G), IC2.10 (GND), IC2.19 (G), IC3.1 (G), IC3.6 (A3), IC3.8 (A4), IC3.10 (GND), IC3.19 (G), IC4.14 (VSS), IC5.7 (GND), IC6.3 (GND), IC6.5 (EN), IC8.7 (GND), IC10.7 (GND), J2_DATA_AND_POWER_CON.2, LD1117V33.IN (GND), U$1.P$8 (GND), U$1.P$29 (GND2), U$1.P$37 (GND3), U$2.1, U$2.2
IN*: IC3.15 (A3), U$1.P$19 (IN*)
INT: IC5.8 (O), IC8.1 (I0), IC8.2 (I1)
INT0*: IC5.12 (I7), J1-INTERRUPTS.1, RN2.2
INT1*: IC5.11 (I6), J1-INTERRUPTS.3, RN2.3
INT2*: IC5.6 (I5), J1-INTERRUPTS.5, RN2.4
INT3*: IC5.5 (I4), J1-INTERRUPTS.7, RN2.5
INT4*: IC5.1 (I0), J1-INTERRUPTS.2, RN2.9
INT5*: IC5.2 (I1), J1-INTERRUPTS.4, RN2.8
INT6*: IC5.3 (I2), J1-INTERRUPTS.6, RN2.7
INT7*: IC5.4 (I3), J1-INTERRUPTS.8, RN2.6
INT*: IC8.3 (O), U$1.P$21 (INT*)
INTAK*: J2_DATA_AND_POWER_CON.7, U$1.P$14 (INTAK*)
unnamed: D2-1N5824.C, IC6.2 (OUT), L1.1
unnamed: D1.A, R7.2
OUT*: IC3.17 (A4), U$1.P$12 (OUT*)
RAS: IC8.8 (O), IC8.13 (I1)
RAS*: IC3.4 (A2), IC8.9 (I0), IC8.10 (I1), U$1.P$1 (RAS*)
RD*: IC3.11 (A1), U$1.P$15 (RD*)
SYSRES*: J2_DATA_AND_POWER_CON.8, U$1.P$2 (SYSRES*)
VCC: C2.1, C3.1, C4.+, C6.1, C7.1, C8.1, C10.1, IC1.20 (VCC), IC2.20 (VCC), IC3.20 (VCC), IC4.28 (VCC), IC5.14 (VCC), IC8.14 (VCC), IC10.14 (VCC), J2_DATA_AND_POWER_CON.1, LD1117V33.OUT (IN), R7.1, RN1.1, RN2.1
VCC/2: C1.+, J2_DATA_AND_POWER_CON.3, LD1117V33.GND (OUT)
WAIT: IC8.4 (I0), IC8.5 (I1), IC10.8 (O)
WAIT0*: IC10.4 (I3), J2-WAITS.8, RN1.6
WAIT1*: IC10.3 (I2), J2-WAITS.6, RN1.7
WAIT2*: IC10.2 (I1), J2-WAITS.4, RN1.8
WAIT3*: IC10.1 (I0), J2-WAITS.2, RN1.9
WAIT4*: IC10.5 (I4), J2-WAITS.7, RN1.5
WAIT5*: IC10.6 (I5), J2-WAITS.5, RN1.4
WAIT6*: IC10.11 (I6), J2-WAITS.3, RN1.3
WAIT7*: IC10.12 (I7), J2-WAITS.1, RN1.2
WAIT*: IC8.6 (O), U$1.P$33 (WAIT*)
WR*: IC3.13 (A2), U$1.P$13 (WR*)

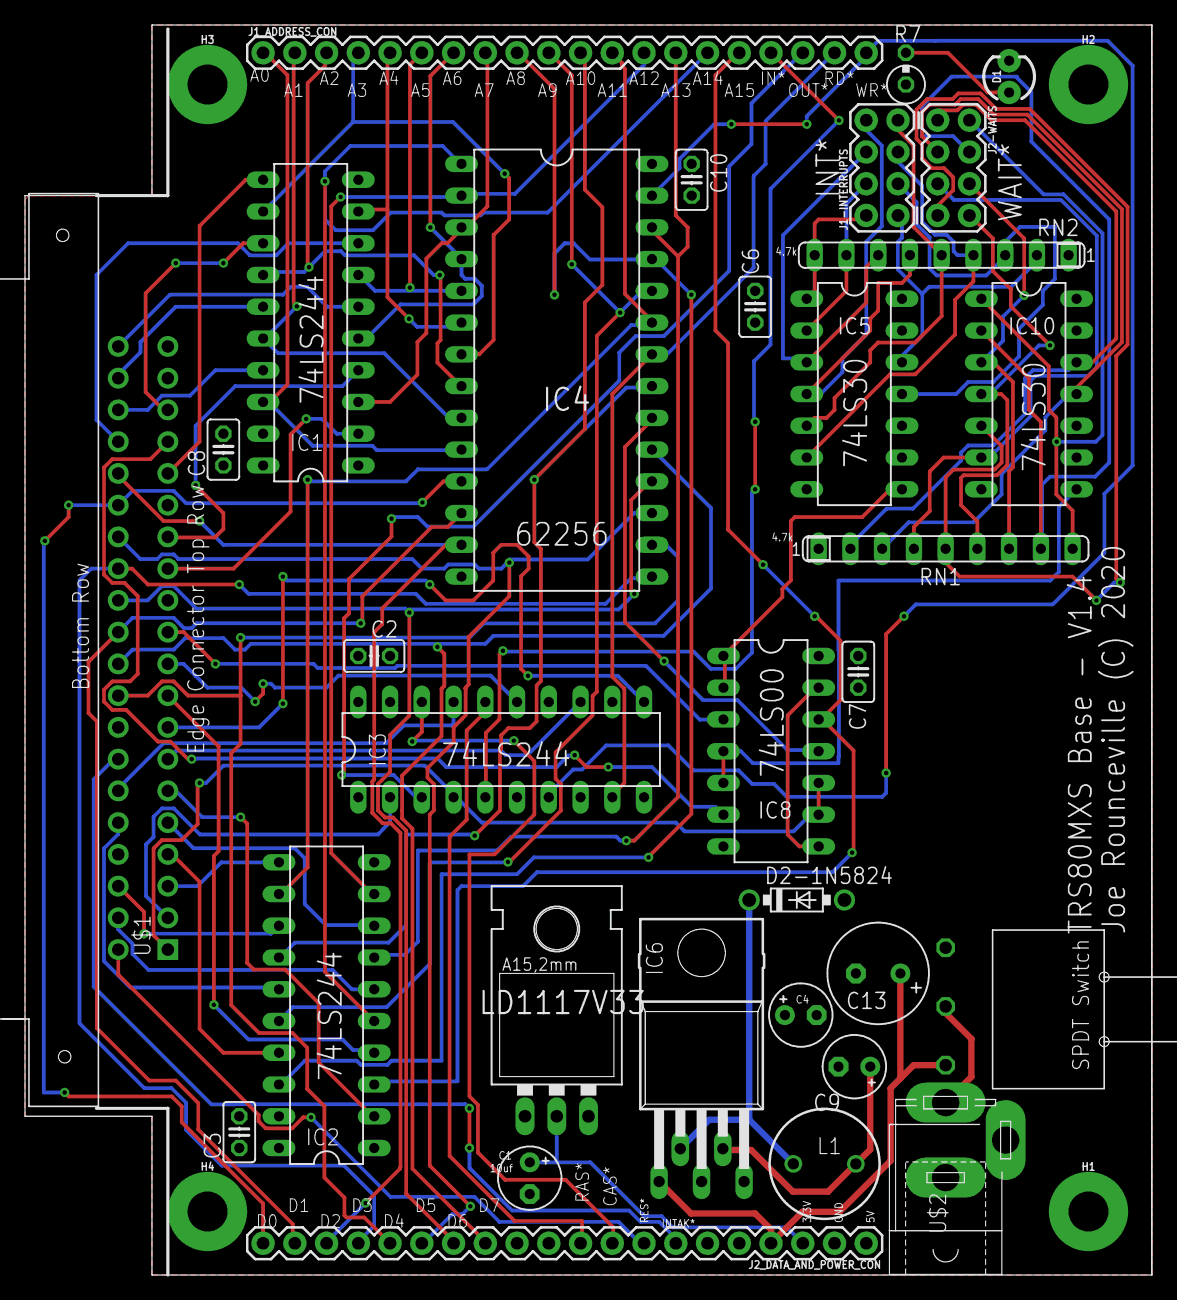
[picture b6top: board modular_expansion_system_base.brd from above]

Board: 2 copper layers, 90.2 x 100.0 mm, 36 parts (0 on the bottom side), 84 nets.
